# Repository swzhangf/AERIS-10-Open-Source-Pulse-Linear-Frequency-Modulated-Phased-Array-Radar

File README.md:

# AERIS-10: Open Source Pulse Linear Frequency Modulated Phased Array Radar

AERIS-10 is an open-source, low-cost 10.5 GHz phased array radar system featuring Pulse Linear Frequency Modulated (LFM) modulation. Available in two versions (3km and 20km range), it's designed for researchers, drone developers, and serious SDR enthusiasts who want to explore and experiment with phased array radar technology.

## 📡 Overview

The AERIS-10 project aims to democratize radar technology by providing a fully open-source, modular, and hackable radar system. Whether you're a university researcher, a drone startup, or an advanced maker, AERIS-10 offers a platform for experimenting with beamforming, pulse compression, Doppler processing, and target tracking.

## 🔬 Key Features

- **Open Source Hardware & Software** - Complete schematics, PCB layouts, firmware, and software available
- **Dual Version Availability**:
  - **AERIS-10N (Nexus)**: 3km range with 8x16 patch antenna array
  - **AERIS-10E (Extended)**: 20km range with 32x16 dielectric-filled slotted waveguide array
- **Full Electronic Beam Steering** - ±45° electronic steering in elevation and azimuth
- **Advanced Signal Processing** - On-board FPGA handles pulse compression, Doppler FFT, MTI, and CFAR
- **Python GUI** - User-friendly interface with map integration
- **GPS/IMU Integration** - Real-time position and attitude correction
- **Modular Design** - Separate power management, frequency synthesis, and RF boards

## 🏗️ System Architecture

### Hardware Components

The AERIS-10 main sub-systems are:

- **Power Management Board** - Supplies all necessary voltage levels to the electronics components with proper filtering and sequencing (sequencing ensured by the microcontroller)

- **Frequency Synthesizer Board** - Uses a high-performance Low Jitter Clock Generator (AD9523-1) that supplies phase-aligned clock references for:
  - RX and TX Frequency Synthesizers (ADF4382)
  - DAC
  - ADC
  - FPGA

- **Main Board** containing:
  - **DAC** - Generates the RADAR Chirps
  - **2x Microwave Mixers (LTC5552)** - For up-conversion and IF-down-conversion
  - **4x 4-Channel Phase Shifters (ADAR1000)** - For RX and TX chain beamforming
  - **16x Front End Chips (ADTR1107)** - Used for both Low Noise Amplifying (RX) and Power Amplifying (TX) stages
  - **XC7A50T FPGA** - Handles RADAR Signal Processing on the upstream FTG256 board:
    - PLFM Chirps generation via the DAC
    - Raw ADC data read
    - Hybrid Automatic Gain Control (AGC) — cross-layer FPGA/STM32/GUI loop
    - I/Q Baseband Down-Conversion
    - Decimation
    - Filtering
    - Forward FFT
    - Pulse Compression
    - Doppler, MTI and CFAR processing
    - USB Interface
  - **STM32F746xx Microcontroller** - Used for:
    - Power-up and power-down sequencing (see Power Management Excel File)
    - FPGA communication
    - Setup and Interface with:
      - Clock Generator (AD9523-1)
      - 2x Frequency Synthesizers (ADF4382)
      - 4x 4-Channel Phase Shifters (ADAR1000) for RADAR pulse sequencing
      - 2x ADS7830 8-channel I²C ADCs (Main Board, U88 @ 0x48 / U89 @ 0x4A) for 16x Idq measurement, one per PA channel, each sensed through a 5 mΩ shunt on the PA board and an INA241A3 current-sense amplifier (x50) on the Main Board
      - 2x DAC5578 8-channel I²C DACs (Main Board, U7 @ 0x48 / U69 @ 0x49) for 16x Vg control, one per PA channel; closed-loop calibrated at boot to the target Idq
      - GPS module (UM982) for GUI map centering and per-detection position tagging
      - GY-85 IMU for pitch/roll correction of target coordinates
      - BMP180 Barometer
      - Stepper Motor
      - 1x ADS7830 8-channel I²C ADC (Main Board, U10) reading 8 thermistors for thermal monitoring; a single GPIO (EN_DIS_COOLING) switches the cooling fans on when any channel exceeds the threshold
      - RF switches

- **16x Power Amplifier Boards** - Used only for AERIS-10E version, featuring 10Watt QPA2962 GaN amplifier for extended range

- **Antenna Arrays**:
  - **AERIS-10N (Nexus)** - 8x16 patch antenna array
  - **AERIS-10X (Extended)** - 32x16 dielectric-filled slotted waveguide antenna array

- **Miscellaneous Components**:
  - Slip-Ring
  - Stepper Motor and drivers
  - Cooling Fans
  - Enclosure

### Processing Pipeline

1. **Waveform Generation** - DAC creates LFM chirps
2. **Up/Down Conversion** - LTC5552 mixers handle frequency translation
3. **Beam Steering** - ADAR1000 phase shifters control 16 elements
4. **Signal Processing (FPGA)**:
   - Raw ADC data capture
   - I/Q baseband down-conversion
   - Decimation & filtering (CIC/FIR)
   - Pulse compression
   - Doppler FFT processing
   - MTI & CFAR detection
5. **System Management (STM32)**:
   - Power sequencing
   - Peripheral configuration
   - GPS/IMU integration
   - Stepper motor control
6. **Visualization (Python GUI)**:
   - Real-time target plotting
   - Map integration
   - Radar control interface

<!-- V6 GIF removed — V6 is deprecated. V65 Tk and V7 PyQt6 are the active GUIs. -->

## 📊 Technical Specifications

| Parameter | AERIS-10N (Nexus) | AERIS-10X (Extended) |
|-----------|-------------------|----------------------|
| **Frequency** | 10.5 GHz | 10.5 GHz |
| **Max Range** | 3 km | 20 km |
| **Antenna** | 8x16 Patch Array | 32x16 Slotted Waveguide |
| **Beam Steering** | Electronic (±45°) | Electronic (±45°) |
| **Mechanical Scan** | 360° (stepper motor) | 360° (stepper motor) |
| **Output Power** | ~1W×16 | 10W×16 (GaN amplifier) |
| **Processing** | FPGA + STM32 | FPGA + STM32 |

## 🚀 Getting Started

### 🧹 Repository File Placement Policy

To keep the repository root clean and make artifacts easy to find, place generated files in the following locations:

- **Published reports (tracked, GitHub Pages):** `docs/`
  - Example: `docs/AERIS_Simulation_Report_v2.pdf`
- **Simulation-generated outputs (local, gitignored):** `5_Simulations/generated/`
  - Plots, scenario outputs, temporary analysis directories
- **FPGA/Vivado generated artifacts (local, gitignored):** `9_Firmware/9_2_FPGA/reports/`
  - VCD/VVP dumps, temporary CSVs, local report snapshots
- **Reusable FPGA automation scripts (tracked):** `9_Firmware/9_2_FPGA/scripts/`
  - TCL flows, helper scripts used by build/bring-up

**Do not leave generated artifacts in the repository root.**

### Prerequisites

- Basic understanding of radar principles
- Experience with PCB assembly (for hardware build)
- Python 3.8+ for the GUI software
- FPGA development tools (Vivado) for signal processing modifications

### Hardware Assembly

1. **Order PCBs**: Production outputs are under `/4_Schematics and Boards Layout/4_7_Production Files`
2. **Source Components**: BOM/CPL files are co-located under `/4_Schematics and Boards Layout/4_7_Production Files`
3. **Assembly**: Use the schematics in `/4_Schematics and Boards Layout/4_6_Schematics` together with the production outputs above; a standalone assembly guide is not currently tracked
4. **Antenna**: Choose appropriate array files for your target variant
5. **Enclosure**: Mechanical drawings currently live in `/8_Utils/Mechanical_Drawings`

## 📜 License

This project is open-source but uses **different licenses for hardware and software** to ensure proper legal coverage.

### Hardware Documentation
The hardware design files—including:
- Schematics and PCB layouts (in `/4_Schematics and Boards Layout`)
- Bill of Materials (BOM) files
- Gerber files and manufacturing outputs
- Mechanical drawings and enclosure designs

are licensed under the **CERN Open Hardware Licence Version 2 – Permissive (CERN-OHL-P)** .

This is a hardware-specific license that:
- ✅ Clearly defines "Hardware," "Documentation," and "Products"
- ✅ Includes explicit patent protection for contributors and users
- ✅ Provides stronger liability limitations (important for high-power RF)
- ✅ Aligns with professional open-hardware standards (CERN, OSHWA)

You may use, modify, and sell products based on these designs, provided you:
- Maintain the original copyright notices
- Distribute any modified designs under the same license
- Make your modifications available in Source format

### Software and Firmware
The software components—including:
- FPGA code (VHDL/Verilog in `/9_Firmware`)
- Microcontroller firmware (STM32)
- Python GUI and utilities

remain under the **MIT License** for maximum flexibility.

### Full License Texts
- The complete CERN-OHL-P license text is in the `LICENSE` file
- MIT license terms apply to software where not otherwise specified

### Why This Change?
Originally, the entire project used the MIT license. The community (special thanks to gmaynez!) pointed out that MIT lacks legal protections needed for physical hardware. The switch to CERN-OHL-P ensures the project is properly protected while maintaining the same permissive spirit.

*Note: This is an active development project. Some features are still in progress. Check the issues page for known limitations and upcoming features.*

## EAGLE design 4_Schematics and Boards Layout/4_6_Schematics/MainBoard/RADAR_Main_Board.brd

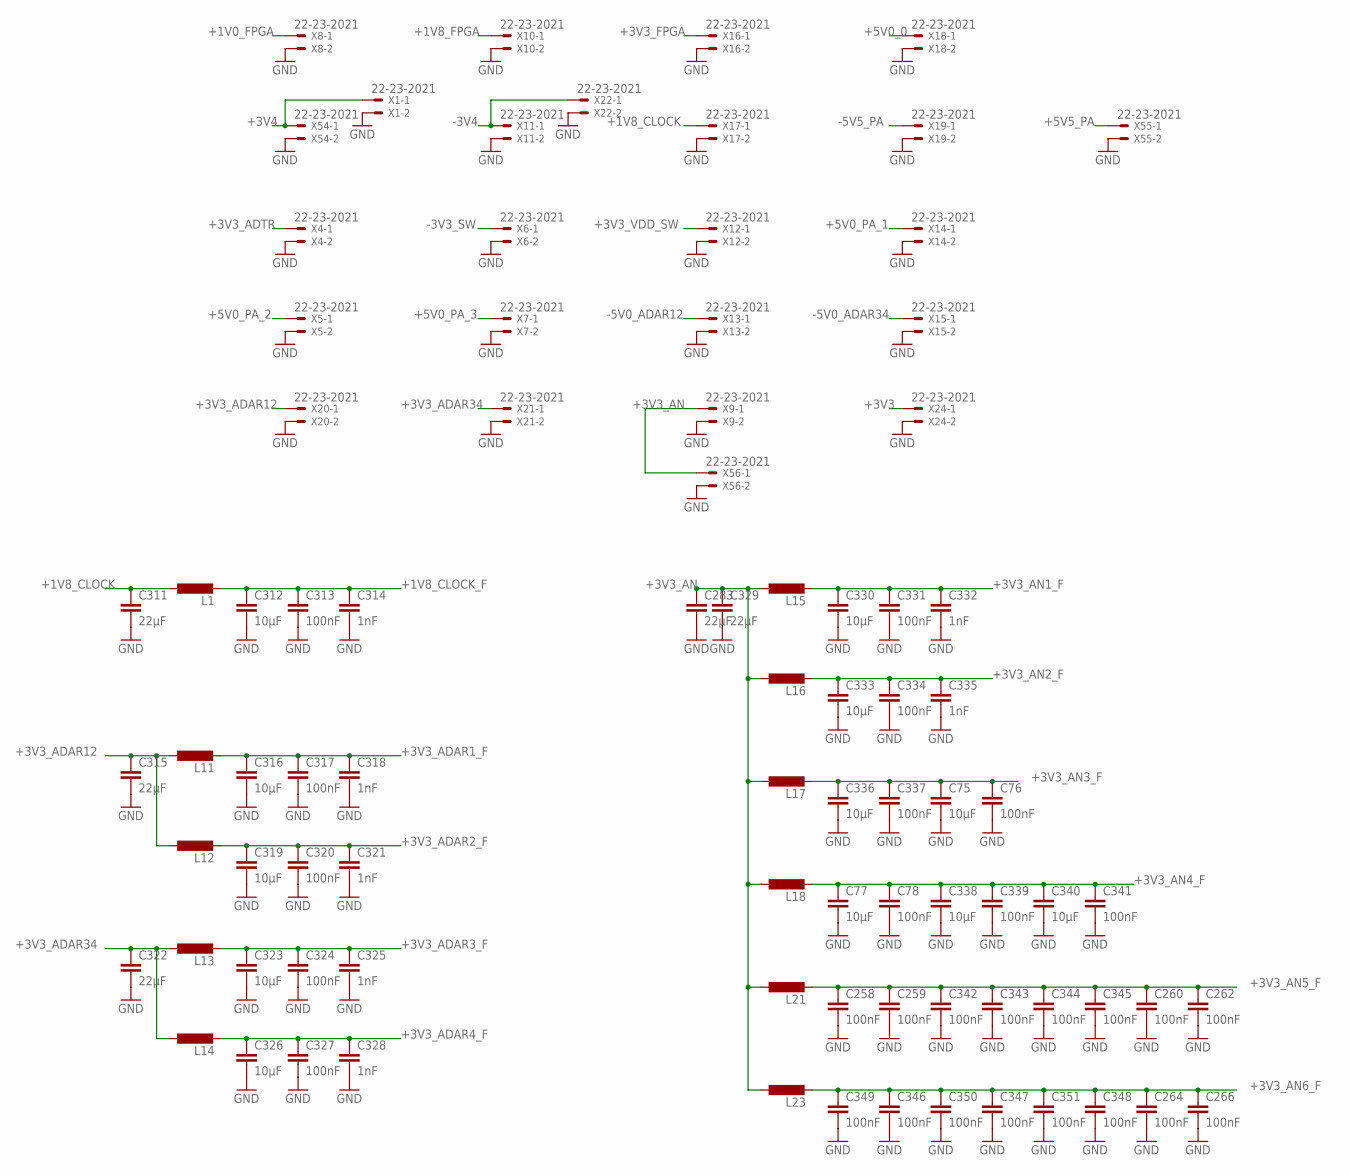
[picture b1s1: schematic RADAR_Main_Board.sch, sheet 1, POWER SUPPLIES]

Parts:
C75, C77, C312, C316, C319, C323, C326, C330, C333, C336, C338, C340: 10µF; C0805
C76, C78, C258, C259, C260, C262, C264, C266, C313, C317, C320, C324, C327, C331, C334, C337, C339, C341, C342, C343, C344, C345, C346, C347, C348, C349, C350, C351: 100nF; C0402
C283, C311, C315, C322, C329: 22µF; C1206
C314, C318, C321, C325, C328, C332, C335: 1nF; C0402
L1, L11, L12, L13, L14, L15, L16, L17, L18, L21, L23: L-EUL5650M; L5650M
X1, X4, X5, X6, X7, X8, X9, X10, X11, X12, X13, X14, X15, X16, X17, X18, X19, X20, X21, X22, X24, X54, X55, X56: 22-23-2021

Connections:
+1V0_FPGA: X8.1; also elsewhere on the board
+1V8_CLOCK: C311.1, L1.1, X17.1
+1V8_CLOCK_F: C312.1, C313.1, C314.1, L1.2; also elsewhere on the board
+1V8_FPGA: X10.1; also elsewhere on the board
+3V3: X24.1; also elsewhere on the board
+3V3_ADAR1_F: C316.1, C317.1, C318.1, L11.2; also elsewhere on the board
+3V3_ADAR2_F: C319.1, C320.1, C321.1, L12.2; also elsewhere on the board
+3V3_ADAR3_F: C323.1, C324.1, C325.1, L13.2; also elsewhere on the board
+3V3_ADAR4_F: C326.1, C327.1, C328.1, L14.2; also elsewhere on the board
+3V3_ADAR12: C315.1, L11.1, L12.1, X20.1
+3V3_ADAR34: C322.1, L13.1, L14.1, X21.1
+3V3_ADTR: X4.1; also elsewhere on the board
+3V3_AN: C283.1, C329.1, L15.1, L16.1, L17.1, L18.1, L21.1, L23.1, X9.1, X56.1; also elsewhere on the board
+3V3_AN1_F: C330.1, C331.1, C332.1, L15.2; also elsewhere on the board
+3V3_AN2_F: C333.1, C334.1, C335.1, L16.2; also elsewhere on the board
+3V3_AN3_F: C75.1, C76.1, C336.1, C337.1, L17.2; also elsewhere on the board
+3V3_AN4_F: C77.1, C78.1, C338.1, C339.1, C340.1, C341.1, L18.2; also elsewhere on the board
+3V3_AN5_F: C258.1, C259.1, C260.1, C262.1, C342.1, C343.1, C344.1, C345.1, L21.2; also elsewhere on the board
+3V3_AN6_F: C264.1, C266.1, C346.1, C347.1, C348.1, C349.1, C350.1, C351.1, L23.2; also elsewhere on the board
+3V3_FPGA: X16.1; also elsewhere on the board
+3V3_VDD_SW: X12.1; also elsewhere on the board
+3V4: X1.1, X54.1; also elsewhere on the board
+5V0_0: X18.1; also elsewhere on the board
+5V0_PA_1: X14.1; also elsewhere on the board
+5V0_PA_2: X5.1; also elsewhere on the board
+5V0_PA_3: X7.1; also elsewhere on the board
+5V5_PA: X55.1; also elsewhere on the board
-3V3_SW: X6.1; also elsewhere on the board
-3V4: X11.1, X22.1; also elsewhere on the board
-5V0_ADAR12: X13.1; also elsewhere on the board
-5V0_ADAR34: X15.1; also elsewhere on the board
-5V5_PA: X19.1; also elsewhere on the board
GND: C75.2, C76.2, C77.2, C78.2, C258.2, C259.2, C260.2, C262.2, C264.2, C266.2, C283.2, C311.2, C312.2, C313.2, C314.2, C315.2, C316.2, C317.2, C318.2, C319.2, C320.2, C321.2, C322.2, C323.2, C324.2, C325.2, C326.2, C327.2, C328.2, C329.2, C330.2, C331.2, C332.2, C333.2, C334.2, C335.2, C336.2, C337.2, C338.2, C339.2, C340.2, C341.2, C342.2, C343.2, C344.2, C345.2, C346.2, C347.2, C348.2, C349.2, C350.2, C351.2, X1.2, X4.2, X5.2, X6.2, X7.2, X8.2, X9.2, X10.2, X11.2, X12.2, X13.2, X14.2, X15.2, X16.2, X17.2, X18.2, X19.2, X20.2, X21.2, X22.2, X24.2, X54.2, X55.2, X56.2; also elsewhere on the board

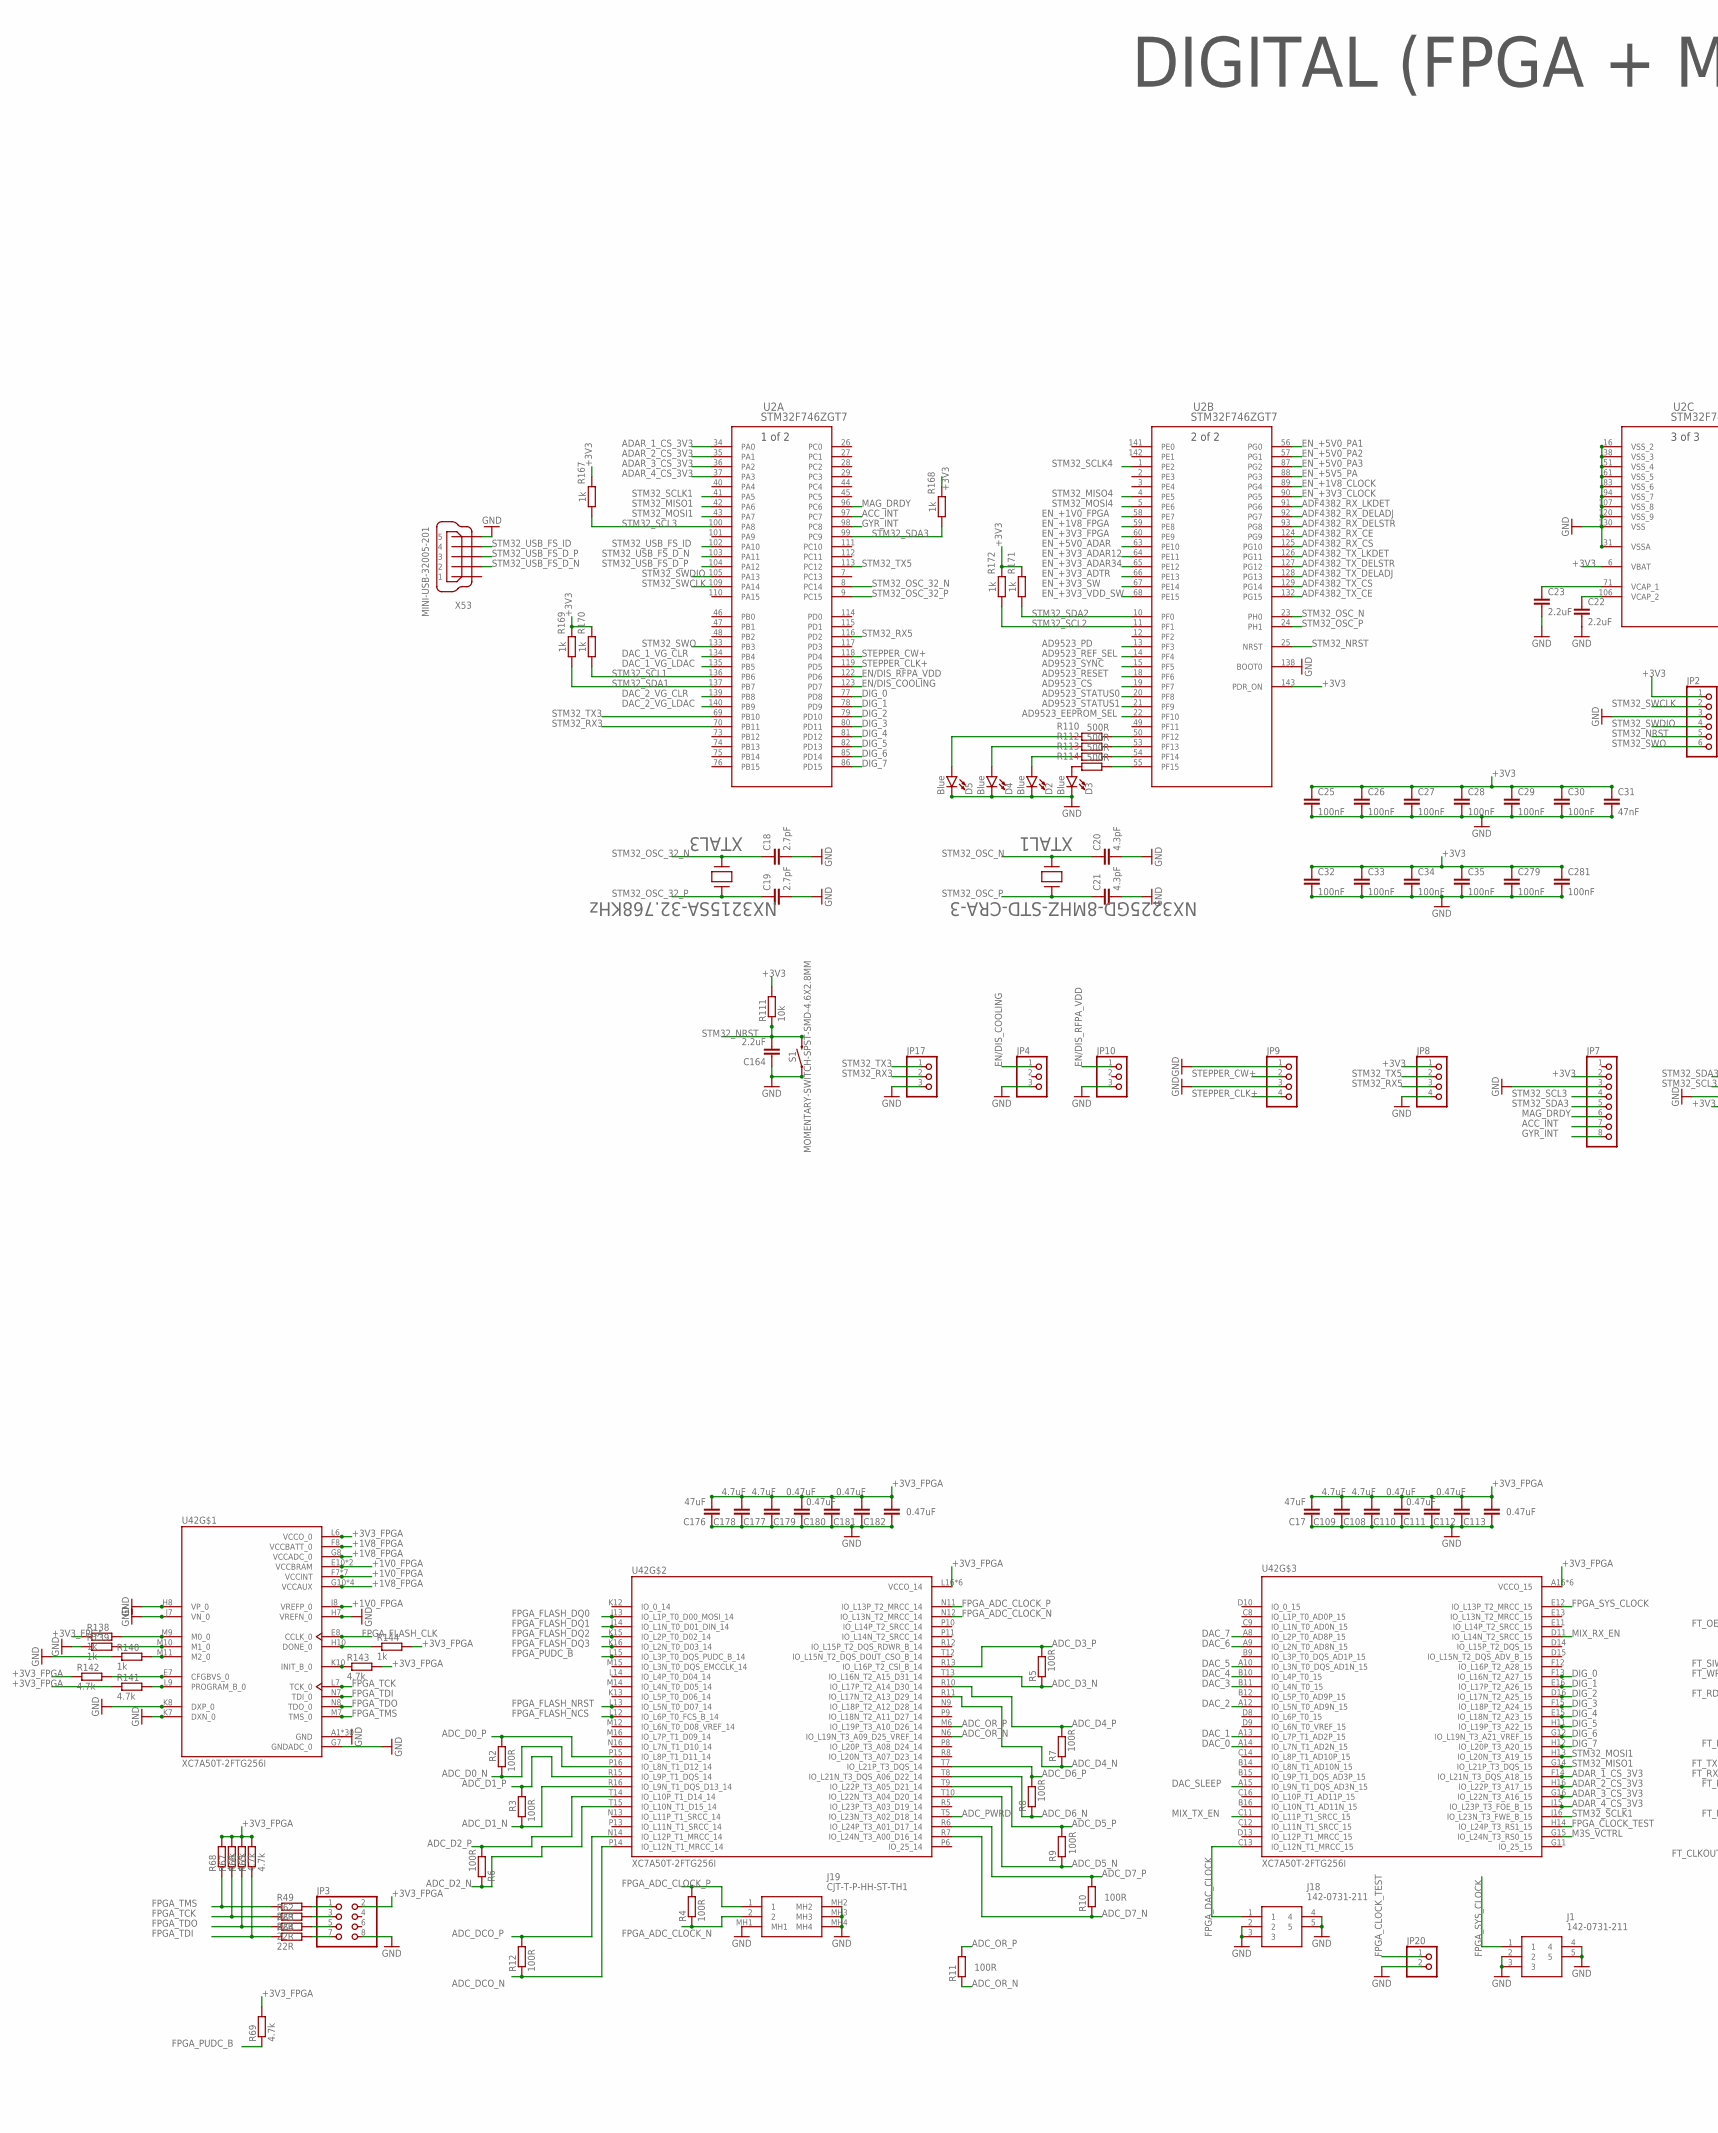
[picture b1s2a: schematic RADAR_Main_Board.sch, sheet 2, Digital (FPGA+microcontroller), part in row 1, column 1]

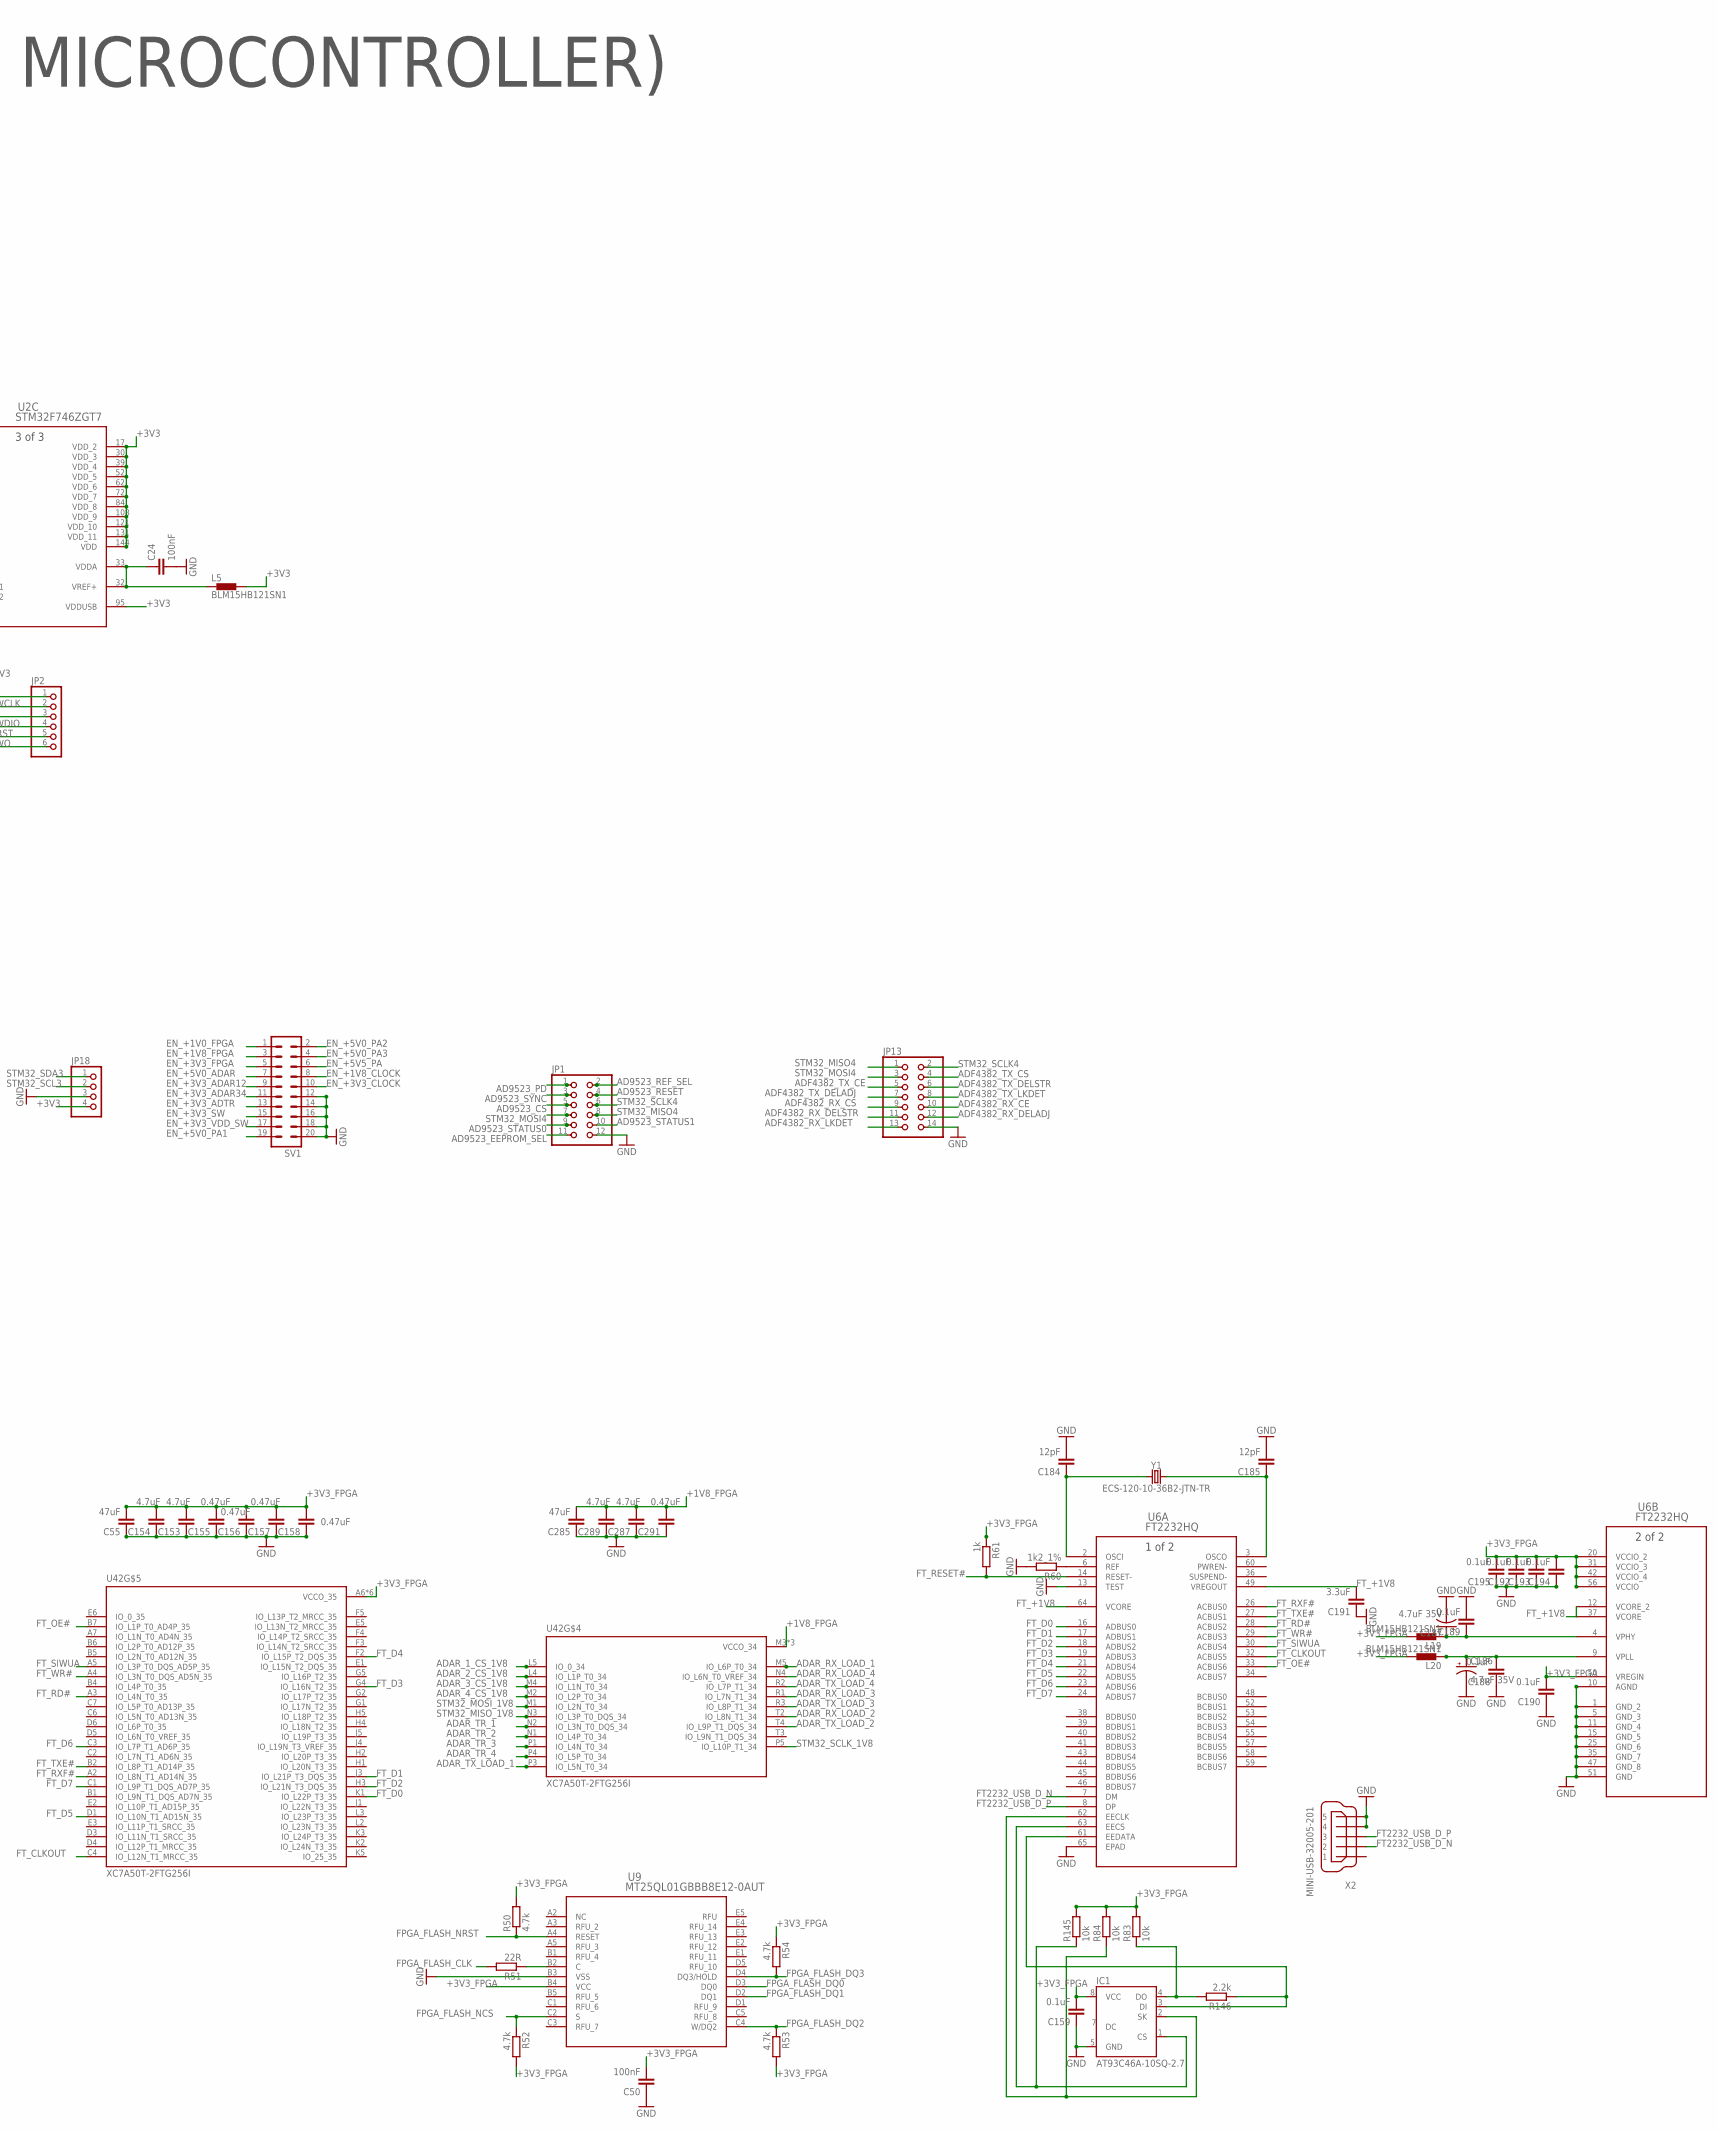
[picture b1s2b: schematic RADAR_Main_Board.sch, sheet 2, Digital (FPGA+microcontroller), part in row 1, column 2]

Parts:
C17, C55, C176, C285: 47uF; C0201
C18, C19: 2.7pF; C0201
C20, C21: 4.3pF; C0201
C22, C23, C164: 2.2uF; C0201
C24, C25, C26, C27, C28, C29, C30, C32, C33, C34, C35, C50, C279, C281: 100nF; C0201
C31: 47nF; C0201
C108, C109, C153, C154, C177, C178, C287, C289: 4.7uF; C0201
C110, C111, C112, C113, C155, C156, C157, C158, C179, C180, C181, C182, C291: 0.47uF; C0201
C159, C188, C189, C190, C192, C193, C194, C195: 0.1uF; C0201
C184, C185: 12pF; C0201
C186, C187: 4.7uF 35V; EIA3528
C191: 3.3uF; C0201
D2, D3, D4, D5: Blue; LED-0603
IC1: AT93C46A-10SQ-2.7; SOIC8
J1, J18: 142-0731-211; 1420731211
J19: CJT-T-P-HH-ST-TH1; CJTTPHHSTTH1
JP1: PINHD-2X6; 2X06
JP2: PINHD-1X6; 1X06
JP3: PINHD-2X4; 2X04
JP4, JP10, JP17: PINHD-1X3; 1X03
JP7: PINHD-1X8; 1X08
JP8, JP9, JP18: PINHD-1X4; 1X04
JP13: PINHD-2X7; 2X07
JP20: PINHD-1X2; 1X02
L5, L19, L20: BLM15HB121SN1; 0402
R2, R3, R4, R5, R6, R7, R8, R9, R10, R11, R12: 100R; R0201
R49, R51, R62, R63, R64: 22R; R0201
R50, R52, R53, R54, R65, R66, R67, R68, R69, R141, R142, R143: 4.7k; R0201
R60: 1k2_1%; R0201
R61, R138, R139, R140, R144, R167, R168, R169, R170, R171, R172: 1k; R0201
R83, R84, R111, R145: 10k; R0201
R110, R112, R113, R114: 500R; R0201
R146: 2.2k; R0201
S1: MOMENTARY-SWITCH-SPST-SMD-4.6X2.8MM; TACTILE_SWITCH_SMD_4.6X2.8MM
SV1: MA10-2
U2: STM32F746ZGT7; LQFP-144_STM
U6: FT2232HQ; 64QFN_FT2232HQ_FTD
U9: MT25QL01GBBB8E12-0AUT; BGA24_MT25QL_MRN
U42: XC7A50T-2FTG256I; BGA256C100P16X16_1700X1700X155
X2, X53: MINI-USB-32005-201; 32005-201
XTAL1: NX3225GD-8MHZ-STD-CRA-3; XTAL_NX3225GD-8MHZ-STD-CRA-3_N
XTAL3: NX3215SA-32.768KHz; XTAL_NX3225GD-8MHZ-STD-CRA-3_N
Y1: ECS-120-10-36B2-JTN-TR; CRYSTAL-SMD-2X2.5MM

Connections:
+1V0_FPGA: U42.E10 (VCCBRAM), U42.F7 (VCCINT), U42.F9 (VCCINT), U42.F11 (VCCBRAM), U42.G6 (VCCINT), U42.H9 (VCCINT), U42.J6 (VCCINT), U42.J8 (VREFP_0), U42.K9 (VCCINT), U42.L8 (VCCINT); also elsewhere on the board
+1V8_FPGA: C285.2, C287.2, C289.2, C291.2, U42.F8 (VCCBATT_0), U42.G8 (VCCADC_0), U42.G10 (VCCAUX), U42.J10 (VCCAUX), U42.K11 (VCCAUX), U42.L10 (VCCAUX), U42.M3 (VCCO_34), U42.R4 (VCCO_34), U42.T1 (VCCO_34); also elsewhere on the board
+3V3: C25.1, C26.1, C27.1, C28.1, C29.1, C30.1, C31.1, C32.1, C33.1, C34.1, C35.1, C279.1, C281.1, JP2.1, JP7.2, JP8.1, JP18.4, L5.2, R111.2, R167.1, R168.1, R169.1, R170.1, R171.1, R172.1, U2.6 (VBAT), U2.17 (VDD_2), U2.30 (VDD_3), U2.39 (VDD_4), U2.52 (VDD_5), U2.62 (VDD_6), U2.72 (VDD_7), U2.84 (VDD_8), U2.95 (VDDUSB), U2.108 (VDD_9), U2.121 (VDD_10), U2.131 (VDD_11), U2.143 (PDR_ON), U2.144 (VDD); also elsewhere on the board
+3V3_FPGA: C17.2, C50.2, C55.2, C108.2, C109.2, C110.2, C111.2, C112.2, C113.2, C153.2, C154.2, C155.2, C156.2, C157.2, C158.2, C159.2, C176.2, C177.2, C178.2, C179.2, C180.2, C181.2, C182.2, C190.2, C192.2, C193.2, C194.2, C195.2, IC1.8 (VCC), JP3.2, L19.2, L20.2, R50.2, R52.2, R53.2, R54.1, R61.1, R65.2, R66.2, R67.2, R68.2, R69.2, R83.2, R84.2, R138.1, R141.1, R142.1, R143.2, R144.2, R145.2, U6.20 (VCCIO_2), U6.31 (VCCIO_3), U6.42 (VCCIO_4), U6.50 (VREGIN), U6.56 (VCCIO), U9.B4 (VCC), U42.A6 (VCCO_35), U42.A16 (VCCO_15), U42.B3 (VCCO_35), U42.B13 (VCCO_15), U42.C10 (VCCO_15), U42.D7 (VCCO_35), U42.E4 (VCCO_35), U42.E14 (VCCO_15), U42.F1 (VCCO_35), U42.H15 (VCCO_15), U42.J2 (VCCO_35), U42.J12 (VCCO_15), U42.L6 (VCCO_0), U42.L16 (VCCO_14), U42.M13 (VCCO_14), U42.N10 (VCCO_14), U42.P7 (VCCO_14), U42.R14 (VCCO_14), U42.T11 (VCCO_14); also elsewhere on the board
ACC_INT: JP7.7, U2.97 (PC7)
AD9523_CS: JP1.5, U2.19 (PF7)
AD9523_EEPROM_SEL: JP1.11, U2.22 (PF10)
AD9523_PD: JP1.1, U2.13 (PF3)
AD9523_REF_SEL: JP1.2, U2.14 (PF4)
AD9523_RESET: JP1.4, U2.18 (PF6)
AD9523_STATUS0: JP1.9, U2.20 (PF8)
AD9523_STATUS1: JP1.10, U2.21 (PF9)
AD9523_SYNC: JP1.3, U2.15 (PF5)
ADAR_1_CS_1V8: U42.L5 (IO_0_34); also elsewhere on the board
ADAR_1_CS_3V3: U2.34 (PA0), U42.F14 (IO_L21N_T3_DQS_A18_15)
ADAR_2_CS_1V8: U42.L4 (IO_L1P_T0_34); also elsewhere on the board
ADAR_2_CS_3V3: U2.35 (PA1), U42.H16 (IO_L22P_T3_A17_15)
ADAR_3_CS_1V8: U42.M4 (IO_L1N_T0_34); also elsewhere on the board
ADAR_3_CS_3V3: U2.36 (PA2), U42.G16 (IO_L22N_T3_A16_15)
ADAR_4_CS_1V8: U42.M2 (IO_L2P_T0_34); also elsewhere on the board
ADAR_4_CS_3V3: U2.37 (PA3), U42.J15 (IO_L23P_T3_FOE_B_15)
ADAR_RX_LOAD_1: U42.M5 (IO_L6P_T0_34); also elsewhere on the board
ADAR_RX_LOAD_2: U42.T2 (IO_L8N_T1_34); also elsewhere on the board
ADAR_RX_LOAD_3: U42.R1 (IO_L7N_T1_34); also elsewhere on the board
ADAR_RX_LOAD_4: U42.N4 (IO_L6N_T0_VREF_34); also elsewhere on the board
ADAR_TR_1: U42.N2 (IO_L3N_T0_DQS_34); also elsewhere on the board
ADAR_TR_2: U42.N1 (IO_L4P_T0_34); also elsewhere on the board
ADAR_TR_3: U42.P1 (IO_L4N_T0_34); also elsewhere on the board
ADAR_TR_4: U42.P4 (IO_L5P_T0_34); also elsewhere on the board
ADAR_TX_LOAD_1: U42.P3 (IO_L5N_T0_34); also elsewhere on the board
ADAR_TX_LOAD_2: U42.T4 (IO_L9P_T1_DQS_34); also elsewhere on the board
ADAR_TX_LOAD_3: U42.R3 (IO_L8P_T1_34); also elsewhere on the board
ADAR_TX_LOAD_4: U42.R2 (IO_L7P_T1_34); also elsewhere on the board
ADC_D0_N: R2.1, U42.P16 (IO_L8N_T1_D12_14); also elsewhere on the board
ADC_D0_P: R2.2, U42.P15 (IO_L8P_T1_D11_14); also elsewhere on the board
ADC_D1_N: R3.1, U42.R16 (IO_L9N_T1_DQS_D13_14); also elsewhere on the board
ADC_D1_P: R3.2, U42.R15 (IO_L9P_T1_DQS_14); also elsewhere on the board
ADC_D2_N: R6.1, U42.T15 (IO_L10N_T1_D15_14); also elsewhere on the board
ADC_D2_P: R6.2, U42.T14 (IO_L10P_T1_D14_14); also elsewhere on the board
ADC_D3_N: R5.1, U42.T13 (IO_L16N_T2_A15_D31_14); also elsewhere on the board
ADC_D3_P: R5.2, U42.R13 (IO_L16P_T2_CSI_B_14); also elsewhere on the board
ADC_D4_N: R7.1, U42.R11 (IO_L17N_T2_A13_D29_14); also elsewhere on the board
ADC_D4_P: R7.2, U42.R10 (IO_L17P_T2_A14_D30_14); also elsewhere on the board
ADC_D5_N: R9.1, U42.T10 (IO_L22N_T3_A04_D20_14); also elsewhere on the board
ADC_D5_P: R9.2, U42.T9 (IO_L22P_T3_A05_D21_14); also elsewhere on the board
ADC_D6_N: R8.1, U42.T8 (IO_L21N_T3_DQS_A06_D22_14); also elsewhere on the board
ADC_D6_P: R8.2, U42.T7 (IO_L21P_T3_DQS_14); also elsewhere on the board
ADC_D7_N: R10.1, U42.R7 (IO_L24N_T3_A00_D16_14); also elsewhere on the board
ADC_D7_P: R10.2, U42.R6 (IO_L24P_T3_A01_D17_14); also elsewhere on the board
ADC_DCO_N: R12.1, U42.P14 (IO_L12N_T1_MRCC_14); also elsewhere on the board
ADC_DCO_P: R12.2, U42.N14 (IO_L12P_T1_MRCC_14); also elsewhere on the board
ADC_OR_N: R11.1, U42.N6 (IO_L19N_T3_A09_D25_VREF_14); also elsewhere on the board
ADC_OR_P: R11.2, U42.M6 (IO_L19P_T3_A10_D26_14); also elsewhere on the board
ADC_PWRD: U42.T5 (IO_L23N_T3_A02_D18_14); also elsewhere on the board
ADF4382_RX_CE: JP13.10, U2.124 (PG9)
ADF4382_RX_CS: JP13.9, U2.125 (PG10)
ADF4382_RX_DELADJ: JP13.12, U2.92 (PG7)
ADF4382_RX_DELSTR: JP13.11, U2.93 (PG8)
ADF4382_RX_LKDET: JP13.13, U2.91 (PG6)
ADF4382_TX_CE: JP13.5, U2.132 (PG15)
ADF4382_TX_CS: JP13.4, U2.129 (PG14)
ADF4382_TX_DELADJ: JP13.7, U2.128 (PG13)
ADF4382_TX_DELSTR: JP13.6, U2.127 (PG12)
ADF4382_TX_LKDET: JP13.8, U2.126 (PG11)
DAC_0: U42.A14 (IO_L7N_T1_AD2N_15); also elsewhere on the board
DAC_1: U42.A13 (IO_L7P_T1_AD2P_15); also elsewhere on the board
DAC_1_VG_CLR: U2.134 (PB4); also elsewhere on the board
DAC_1_VG_LDAC: U2.135 (PB5); also elsewhere on the board
DAC_2: U42.A12 (IO_L5N_T0_AD9N_15); also elsewhere on the board
DAC_2_VG_CLR: U2.139 (PB8); also elsewhere on the board
DAC_2_VG_LDAC: U2.140 (PB9); also elsewhere on the board
DAC_3: U42.B11 (IO_L4N_T0_15); also elsewhere on the board
DAC_4: U42.B10 (IO_L4P_T0_15); also elsewhere on the board
DAC_5: U42.A10 (IO_L3N_T0_DQS_AD1N_15); also elsewhere on the board
DAC_6: U42.A9 (IO_L2N_T0_AD8N_15); also elsewhere on the board
DAC_7: U42.A8 (IO_L2P_T0_AD8P_15); also elsewhere on the board
DAC_SLEEP: U42.A15 (IO_L9N_T1_DQS_AD3N_15); also elsewhere on the board
DIG_0: U2.77 (PD8), U42.F13 (IO_L16N_T2_A27_15)
DIG_1: U2.78 (PD9), U42.E16 (IO_L17P_T2_A26_15)
DIG_2: U2.79 (PD10), U42.D16 (IO_L17N_T2_A25_15)
DIG_3: U2.80 (PD11), U42.F15 (IO_L18P_T2_A24_15)
DIG_4: U2.81 (PD12), U42.E15 (IO_L18N_T2_A23_15)
DIG_5: U2.82 (PD13), U42.H11 (IO_L19P_T3_A22_15)
DIG_6: U2.85 (PD14), U42.G12 (IO_L19N_T3_A21_VREF_15)
DIG_7: U2.86 (PD15), U42.H12 (IO_L20P_T3_A20_15)
EN/DIS_COOLING: JP4.1, U2.123 (PD7)
EN/DIS_RFPA_VDD: JP10.1, U2.122 (PD6)
EN_+1V0_FPGA: SV1.1, U2.58 (PE7)
EN_+1V8_CLOCK: SV1.8, U2.89 (PG4)
EN_+1V8_FPGA: SV1.3, U2.59 (PE8)
EN_+3V3_ADAR12: SV1.9, U2.64 (PE11)
EN_+3V3_ADAR34: SV1.11, U2.65 (PE12)
EN_+3V3_ADTR: SV1.13, U2.66 (PE13)
EN_+3V3_CLOCK: SV1.10, U2.90 (PG5)
EN_+3V3_FPGA: SV1.5, U2.60 (PE9)
EN_+3V3_SW: SV1.15, U2.67 (PE14)
EN_+3V3_VDD_SW: SV1.17, U2.68 (PE15)
EN_+5V0_ADAR: SV1.7, U2.63 (PE10)
EN_+5V0_PA1: SV1.19, U2.56 (PG0)
EN_+5V0_PA2: SV1.2, U2.57 (PG1)
EN_+5V0_PA3: SV1.4, U2.87 (PG2)
EN_+5V5_PA: SV1.6, U2.88 (PG3)
FPGA_ADC_CLOCK_N: J19.2, R4.1, U42.N12 (IO_L13N_T2_MRCC_14)
FPGA_ADC_CLOCK_P: J19.1, R4.2, U42.N11 (IO_L13P_T2_MRCC_14)
FPGA_CLOCK_TEST: JP20.1, U42.H14 (IO_L24P_T3_RS1_15)
FPGA_DAC_CLOCK: J18.1, U42.C13 (IO_L12N_T1_MRCC_15)
FPGA_FLASH_CLK: R51.2, U42.E8 (CCLK_0)
FPGA_FLASH_DQ0: U9.D3 (DQ0), U42.J13 (IO_L1P_T0_D00_MOSI_14)
FPGA_FLASH_DQ1: U9.D2 (DQ1), U42.J14 (IO_L1N_T0_D01_DIN_14)
FPGA_FLASH_DQ2: R53.1, U9.C4 (W/DQ2), U42.K15 (IO_L2P_T0_D02_14)
FPGA_FLASH_DQ3: R54.2, U9.D4 (DQ3/HOLD), U42.K16 (IO_L2N_T0_D03_14)
FPGA_FLASH_NCS: R52.1, U9.C2 (S), U42.L12 (IO_L6P_T0_FCS_B_14)
FPGA_FLASH_NRST: R50.1, U9.A4 (RESET), U42.L13 (IO_L5N_T0_D07_14)
FPGA_PUDC_B: R69.1, U42.L15 (IO_L3P_T0_DQS_PUDC_B_14)
FPGA_SYS_CLOCK: J1.1, U42.E12 (IO_L13P_T2_MRCC_15)
FPGA_TCK: R62.1, R67.1, U42.L7 (TCK_0)
FPGA_TDI: R64.1, R65.1, U42.N7 (TDI_0)
FPGA_TDO: R63.1, R66.1, U42.N8 (TDO_0)
FPGA_TMS: R49.1, R68.1, U42.M7 (TMS_0)
FT2232_USB_D_N: U6.7 (DM), X2.2
FT2232_USB_D_P: U6.8 (DP), X2.3
FT_+1V8: C191.2, U6.12 (VCORE_2), U6.37 (VCORE), U6.49 (VREGOUT), U6.64 (VCORE)
FT_CLKOUT: U6.32 (ACBUS5), U42.C4 (IO_L12N_T1_MRCC_35)
FT_D0: U6.16 (ADBUS0), U42.K1 (IO_L22P_T3_35)
FT_D1: U6.17 (ADBUS1), U42.J3 (IO_L21P_T3_DQS_35)
FT_D2: U6.18 (ADBUS2), U42.H3 (IO_L21N_T3_DQS_35)
FT_D3: U6.19 (ADBUS3), U42.G4 (IO_L16N_T2_35)
FT_D4: U6.21 (ADBUS4), U42.F2 (IO_L15P_T2_DQS_35)
FT_D5: U6.22 (ADBUS5), U42.D1 (IO_L10N_T1_AD15N_35)
FT_D6: U6.23 (ADBUS6), U42.C3 (IO_L7P_T1_AD6P_35)
FT_D7: U6.24 (ADBUS7), U42.C1 (IO_L9P_T1_DQS_AD7P_35)
FT_OE#: U6.33 (ACBUS6), U42.B7 (IO_L1P_T0_AD4P_35)
FT_RD#: U6.28 (ACBUS2), U42.A3 (IO_L4N_T0_35)
FT_RESET#: R61.2, U6.14 (RESET-)
FT_RXF#: U6.26 (ACBUS0), U42.A2 (IO_L8N_T1_AD14N_35)
FT_SIWUA: U6.30 (ACBUS4), U42.A5 (IO_L3P_T0_DQS_AD5P_35)
FT_TXE#: U6.27 (ACBUS1), U42.B2 (IO_L8P_T1_AD14P_35)
FT_WR#: U6.29 (ACBUS3), U42.A4 (IO_L3N_T0_DQS_AD5N_35)
GND: C17.1, C18.2, C19.2, C20.2, C21.2, C22.2, C23.2, C24.2, C25.2, C26.2, C27.2, C28.2, C29.2, C30.2, C31.2, C32.2, C33.2, C34.2, C35.2, C50.1, C55.1, C108.1, C109.1, C110.1, C111.1, C112.1, C113.1, C153.1, C154.1, C155.1, C156.1, C157.1, C158.1, C159.1, C164.1, C176.1, C177.1, C178.1, C179.1, C180.1, C181.1, C182.1, C184.2, C185.2, C186.C (-), C187.C (-), C188.1, C189.2, C190.1, C191.1, C192.1, C193.1, C194.1, C195.1, C279.2, C281.2, C285.1, C287.1, C289.1, C291.1, D2.C, D3.C, D4.C, D5.C, IC1.5 (GND), J1.2, J1.3, J1.4, J1.5, J18.2, J18.3, J18.4, J18.5, J19.MH1, J19.MH2, J19.MH3, J19.MH4, JP1.12, JP2.3, JP3.8, JP4.3, JP7.3, JP8.4, JP9.1, JP9.3, JP10.3, JP13.14, JP17.3, JP18.3, JP20.2, R60.2, R139.1, R140.1, S1.1, S1.2 (1), SV1.12, SV1.14, SV1.16, SV1.18, SV1.20, U2.16 (VSS_2), U2.31 (VSSA), U2.38 (VSS_3), U2.51 (VSS_4), U2.61 (VSS_5), U2.83 (VSS_6), U2.94 (VSS_7), U2.107 (VSS_8), U2.120 (VSS_9), U2.130 (VSS), U2.138 (BOOT0), U6.1 (GND_2), U6.5 (GND_3), U6.10 (AGND), U6.11 (GND_4), U6.13 (TEST), U6.15 (GND_5), U6.25 (GND_6), U6.35 (GND_7), U6.47 (GND_8), U6.51 (GND), U6.65 (EPAD), U9.B3 (VSS), U42.A1 (GND), U42.A11 (GND), U42.B8 (GND), U42.C5 (GND), U42.C15 (GND), U42.D2 (GND), U42.D12 (GND), U42.E9 (GND), U42.F6 (GND), U42.F10 (GND), U42.F16 (GND), U42.G3 (GND), U42.G7 (GNDADC_0), U42.G9 (GND), U42.G13 (GND), U42.H6 (GND), U42.H7 (VREFN_0), U42.H8 (VP_0), U42.J7 (VN_0), U42.J9 (GND), U42.J11 (GND), U42.K4 (GND), U42.K6 (GND), U42.K7 (DXN_0), U42.K8 (DXP_0), U42.K14 (GND), U42.L1 (GND), U42.L11 (GND), U42.M8 (GND), U42.N5 (GND), U42.N15 (GND), U42.P2 (GND), U42.P12 (GND), U42.R9 (GND), U42.T6 (GND), U42.T16 (GND), X2.4, X2.5, X53.5; also elsewhere on the board
GYR_INT: JP7.8, U2.98 (PC8)
M3S_VCTRL: U42.G15 (IO_L24N_T3_RS0_15); also elsewhere on the board
MAG_DRDY: JP7.6, U2.96 (PC6)
MIX_RX_EN: U42.D11 (IO_L14N_T2_SRCC_15); also elsewhere on the board
MIX_TX_EN: U42.C11 (IO_L11P_T1_SRCC_15); also elsewhere on the board
unnamed: C23.1, U2.71 (VCAP_1)
unnamed: C22.1, U2.106 (VCAP_2)
unnamed: C24.1, L5.1, U2.32 (VREF+), U2.33 (VDDA)
unnamed: R51.1, U9.B2 (C)
unnamed: JP3.1, R49.2
unnamed: JP3.3, R62.2
unnamed: JP3.5, R63.2
unnamed: JP3.7, R64.2
unnamed: R110.2, U2.50 (PF12)
unnamed: IC1.4 (DO), R83.1, R146.2
unnamed: R112.2, U2.53 (PF13)
unnamed: D3.A, R114.1
unnamed: R113.2, U2.54 (PF14)
unnamed: R114.2, U2.55 (PF15)
unnamed: D2.A, R113.1
unnamed: D4.A, R112.1
unnamed: D5.A, R110.1
unnamed: R138.2, U42.M9 (M0_0)
unnamed: R139.2, U42.M10 (M1_0)
unnamed: R140.2, U42.M11 (M2_0)
unnamed: R141.2, U42.L9 (PROGRAM_B_0)
unnamed: R142.2, U42.E7 (CFGBVS_0)
unnamed: R144.1, U42.H10 (DONE_0)
unnamed: R143.1, U42.K10 (INIT_B_0)
unnamed: R60.1, U6.6 (REF)
unnamed: C184.1, U6.2 (OSCI), Y1.P1 (1)
unnamed: C185.1, U6.3 (OSCO), Y1.P3 (2)
unnamed: C186.A (+), C188.2, L20.1, U6.9 (VPLL)
unnamed: C187.A (+), C189.1, L19.1, U6.4 (VPHY)
unnamed: IC1.1 (CS), R145.1, U6.63 (EECS)
unnamed: IC1.2 (SK), R84.1, U6.62 (EECLK)
unnamed: IC1.3 (DI), R146.1, U6.61 (EEDATA)
STEPPER_CLK+: JP9.4, U2.119 (PD5)
STEPPER_CW+: JP9.2, U2.118 (PD4)
STM32_MISO1: U2.42 (PA6), U42.G14 (IO_L21P_T3_DQS_15)
STM32_MISO4: JP1.8, JP13.1, U2.4 (PE5)
STM32_MISO_1V8: U42.N3 (IO_L3P_T0_DQS_34); also elsewhere on the board
STM32_MOSI1: U2.43 (PA7), U42.H13 (IO_L20N_T3_A19_15)
STM32_MOSI4: JP1.7, JP13.3, U2.5 (PE6)
STM32_MOSI_1V8: U42.M1 (IO_L2N_T0_34); also elsewhere on the board
STM32_NRST: C164.2, JP2.5, R111.1, S1.3 (2), S1.4 (2), U2.25 (NRST)
STM32_OSC_32_N: C18.1, U2.8 (PC14), XTAL3.2
STM32_OSC_32_P: C19.1, U2.9 (PC15), XTAL3.1
STM32_OSC_N: C20.1, U2.23 (PH0), XTAL1.2
STM32_OSC_P: C21.1, U2.24 (PH1), XTAL1.1
STM32_RX3: JP17.2, U2.70 (PB11)
STM32_RX5: JP8.3, U2.116 (PD2)
STM32_SCL1: R170.2, U2.136 (PB6); also elsewhere on the board
STM32_SCL2: R172.2, U2.11 (PF1); also elsewhere on the board
STM32_SCL3: JP7.4, JP18.2, R167.2, U2.100 (PA8)
STM32_SCLK1: U2.41 (PA5), U42.J16 (IO_L23N_T3_FWE_B_15)
STM32_SCLK4: JP1.6, JP13.2, U2.1 (PE2)
STM32_SCLK_1V8: U42.P5 (IO_L10P_T1_34); also elsewhere on the board
STM32_SDA1: R169.2, U2.137 (PB7); also elsewhere on the board
STM32_SDA2: R171.2, U2.10 (PF0); also elsewhere on the board
STM32_SDA3: JP7.5, JP18.1, R168.2, U2.99 (PC9)
STM32_SWCLK: JP2.2, U2.109 (PA14)
STM32_SWDIO: JP2.4, U2.105 (PA13)
STM32_SWO: JP2.6, U2.133 (PB3)
STM32_TX3: JP17.1, U2.69 (PB10)
STM32_TX5: JP8.2, U2.113 (PC12)
STM32_USB_FS_D_N: U2.103 (PA11), X53.2
STM32_USB_FS_D_P: U2.104 (PA12), X53.3
STM32_USB_FS_ID: U2.102 (PA10), X53.4

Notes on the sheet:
DIGITAL (FPGA + MICROCONTROLLER)

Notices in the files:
9_Firmware/9_1_Microcontroller/9_1_3_C_Cpp_Code/main.cpp:
Copyright (c) 2025 STMicroelectronics.
All rights reserved.
This software is licensed under terms that can be found in the LICENSE file
README.md:
Hardware: CERN-OHL-P
parts and their libraries:
SparkFun-LED: Licensing: Creative Commons ShareAlike 4.0 International - https://creativecommons.org/licenses/by-sa/4.0
COPYRIGHT: Copyright (C) 2024 Ultra Librarian. All rights reserved.
COPYRIGHT: Copyright (C) 2025 Ultra Librarian. All rights reserved.
